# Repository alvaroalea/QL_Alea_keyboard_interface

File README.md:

# QL_Alea_keyboard_interface
A USB Keyboard Interface to install inside Sinclair QL Computer an replace the orignal Keyboard

## WARNING - THIS PROJECT IT'S INCOMPLETE
This is only some work in progress files.

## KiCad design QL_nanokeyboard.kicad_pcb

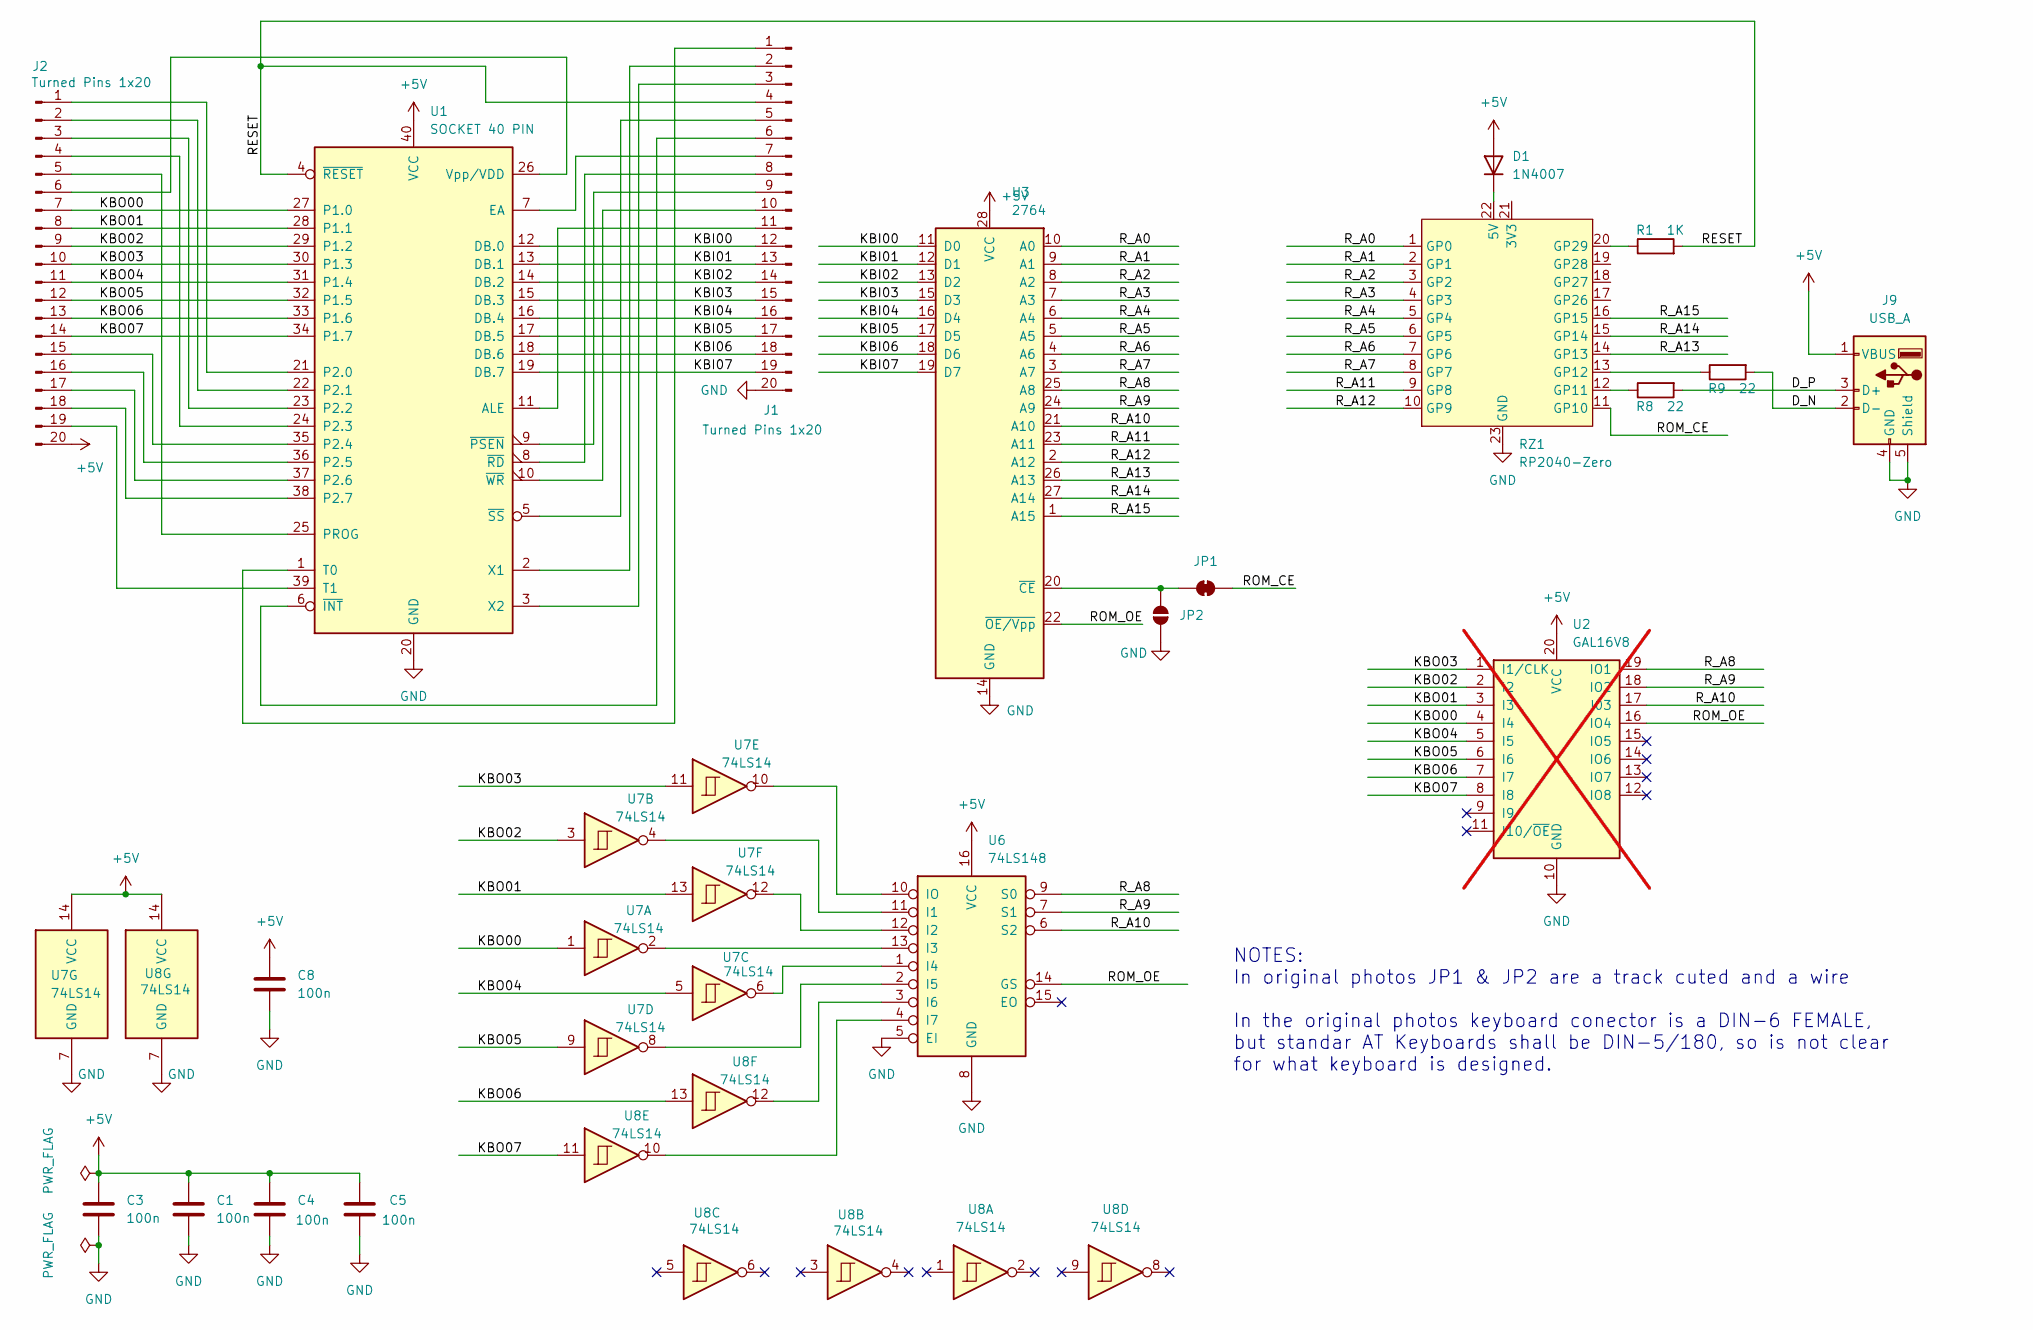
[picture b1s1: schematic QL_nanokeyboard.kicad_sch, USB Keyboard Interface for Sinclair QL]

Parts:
C1, C3, C4, C5: 100n; C_Disc_D4.3mm_W1.9mm_P5.00mm
C8: 100n; C_Disc_D5.0mm_W2.5mm_P5.00mm
D1: 1N4007; D_DO-35_SOD27_P7.62mm_Horizontal
J1, J2: Turned Pins 1x20; PinHeader_1x20_P2.54mm_Vertical
J9: USB_A; USB_A_Molex_67643_Horizontal
JP1: SolderJumper_2_Bridged; SolderJumper-2_P1.3mm_Bridged_Pad1.0x1.5mm
JP2: SolderJumper_2_Open; SolderJumper-2_P1.3mm_Open_Pad1.0x1.5mm
R1: 1K; R_Axial_DIN0207_L6.3mm_D2.5mm_P7.62mm_Horizontal
R8, R9: 22; R_Axial_DIN0207_L6.3mm_D2.5mm_P7.62mm_Horizontal
RZ1: RP2040-Zero
U1: SOCKET 40 PIN; DIP-40_W15.24mm_Socket
U2: GAL16V8; not fitted
U3: 2764; DIP-28_W15.24mm
U6: 74LS148; DIP-16_W7.62mm
U7, U8: 74LS14; DIP-14_W7.62mm

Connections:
+5V: C1.1, C3.1, C4.1, C5.2, C8.1, D1.2 (A), J2.20, J9.1 (VBUS), U1.40 (VCC), U2.20 (VCC), U3.28 (VCC), U6.16 (VCC), U7.14 (VCC), U8.14 (VCC)
/D_N: J9.2 (D-), R9.2
/D_P: J9.3 (D+), R8.2
/KBI00: J1.12, U1.12 (DB.0), U3.11 (D0)
/KBI01: J1.13, U1.13 (DB.1), U3.12 (D1)
/KBI02: J1.14, U1.14 (DB.2), U3.13 (D2)
/KBI03: J1.15, U1.15 (DB.3), U3.15 (D3)
/KBI04: J1.16, U1.16 (DB.4), U3.16 (D4)
/KBI05: J1.17, U1.17 (DB.5), U3.17 (D5)
/KBI06: J1.18, U1.18 (DB.6), U3.18 (D6)
/KBI07: J1.19, U1.19 (DB.7), U3.19 (D7)
/KBO00: J2.7, U1.27 (P1.0), U2.4 (I4), U7.1
/KBO01: J2.8, U1.28 (P1.1), U2.3 (I3), U7.13
/KBO02: J2.9, U1.29 (P1.2), U2.2 (I2), U7.3
/KBO03: J2.10, U1.30 (P1.3), U2.1 (I1/CLK), U7.11
/KBO04: J2.11, U1.31 (P1.4), U2.5 (I5), U7.5
/KBO05: J2.12, U1.32 (P1.5), U2.6 (I6), U7.9
/KBO06: J2.13, U1.33 (P1.6), U2.7 (I7), U8.13
/KBO07: J2.14, U1.34 (P1.7), U2.8 (I8), U8.11
/RESET: J1.4, R1.2, U1.4 (~RESET)
/ROM_CE: JP1.2 (B), RZ1.11 (GP10)
/ROM_OE: U2.16 (IO4), U3.22 (~OE/Vpp), U6.14 (GS)
/R_A0: RZ1.1 (GP0), U3.10 (A0)
/R_A1: RZ1.2 (GP1), U3.9 (A1)
/R_A2: RZ1.3 (GP2), U3.8 (A2)
/R_A3: RZ1.4 (GP3), U3.7 (A3)
/R_A4: RZ1.5 (GP4), U3.6 (A4)
/R_A5: RZ1.6 (GP5), U3.5 (A5)
/R_A6: RZ1.7 (GP6), U3.4 (A6)
/R_A7: RZ1.8 (GP7), U3.3 (A7)
/R_A8: U2.19 (IO1), U3.25 (A8), U6.9 (S0)
/R_A9: U2.18 (IO2), U3.24 (A9), U6.7 (S1)
/R_A10: U2.17 (I03), U3.21 (A10), U6.6 (S2)
/R_A11: RZ1.9 (GP8), U3.23 (A11)
/R_A12: RZ1.10 (GP9), U3.2 (A12)
/R_A13: RZ1.14 (GP13), U3.26 (A13)
/R_A14: RZ1.15 (GP14), U3.27 (A14)
/R_A15: RZ1.16 (GP15), U3.1 (A15)
GND: C1.2, C3.2, C4.2, C5.1, C8.2, J1.20, J9.4 (GND), J9.5 (Shield), JP2.1 (A), RZ1.23 (GND), U1.20 (GND), U2.10 (GND), U3.14 (GND), U6.5 (EI), U6.8 (GND), U7.7 (GND), U8.7 (GND)
unnamed: D1.1 (K), RZ1.22 (5V)
unnamed: J1.1, U1.1 (T0)
unnamed: J1.2, U1.2 (X1)
unnamed: J1.3, U1.3 (X2)
unnamed: J1.5, U1.5 (~SS)
unnamed: J1.6, U1.6 (~INT)
unnamed: J1.7, U1.7 (EA)
unnamed: J1.8, U1.8 (~RD)
unnamed: J1.9, U1.9 (~PSEN)
unnamed: J1.10, U1.10 (~WR)
unnamed: J1.11, U1.11 (ALE)
unnamed: J2.1, U1.21 (P2.0)
unnamed: J2.2, U1.22 (P2.1)
unnamed: J2.3, U1.23 (P2.2)
unnamed: J2.4, U1.24 (P2.3)
unnamed: J2.5, U1.25 (PROG)
unnamed: J2.6, U1.26 (Vpp/VDD)
unnamed: J2.15, U1.35 (P2.4)
unnamed: J2.16, U1.36 (P2.5)
unnamed: J2.17, U1.37 (P2.6)
unnamed: J2.18, U1.38 (P2.7)
unnamed: J2.19, U1.39 (T1)
unnamed: JP1.1 (A), JP2.2 (B), U3.20 (~CE)
unnamed: R8.1, RZ1.12 (GP11)
unnamed: R9.1, RZ1.13 (GP12)
unnamed: R1.1, RZ1.20 (GP29)
unnamed: U6.11 (I1), U7.4
unnamed: U6.12 (I2), U7.12
unnamed: U6.13 (I3), U7.2
unnamed: U6.1 (I4), U7.6
unnamed: U6.2 (I5), U7.8
unnamed: U6.3 (I6), U8.12
unnamed: U6.4 (I7), U8.10
unnamed: U6.10 (IO), U7.10

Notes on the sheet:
NOTES: In original photos JP1 & JP2 are a track cuted and a wire In the original photos keyboard conector is a DIN-6 FEMALE, but standar AT Keyboards shall be DIN-5/180, so is not clear for what keyboard is designed.

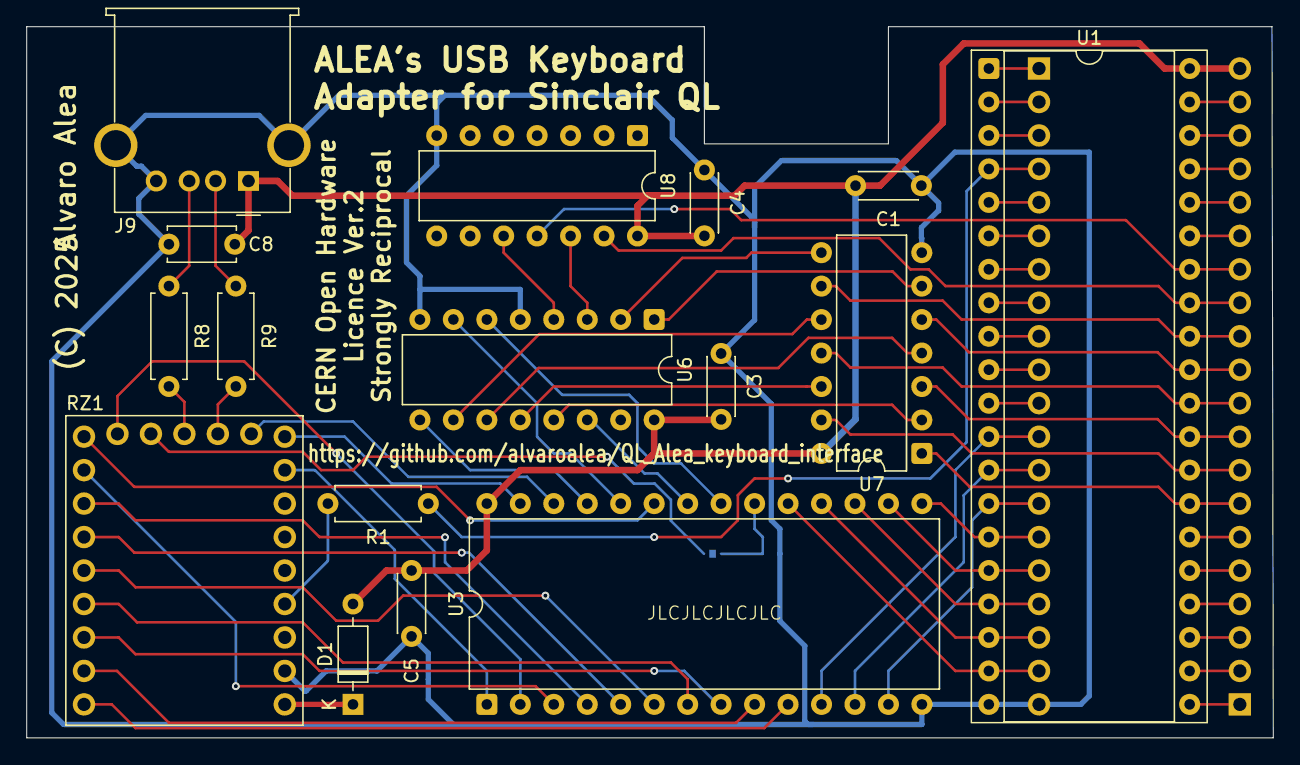
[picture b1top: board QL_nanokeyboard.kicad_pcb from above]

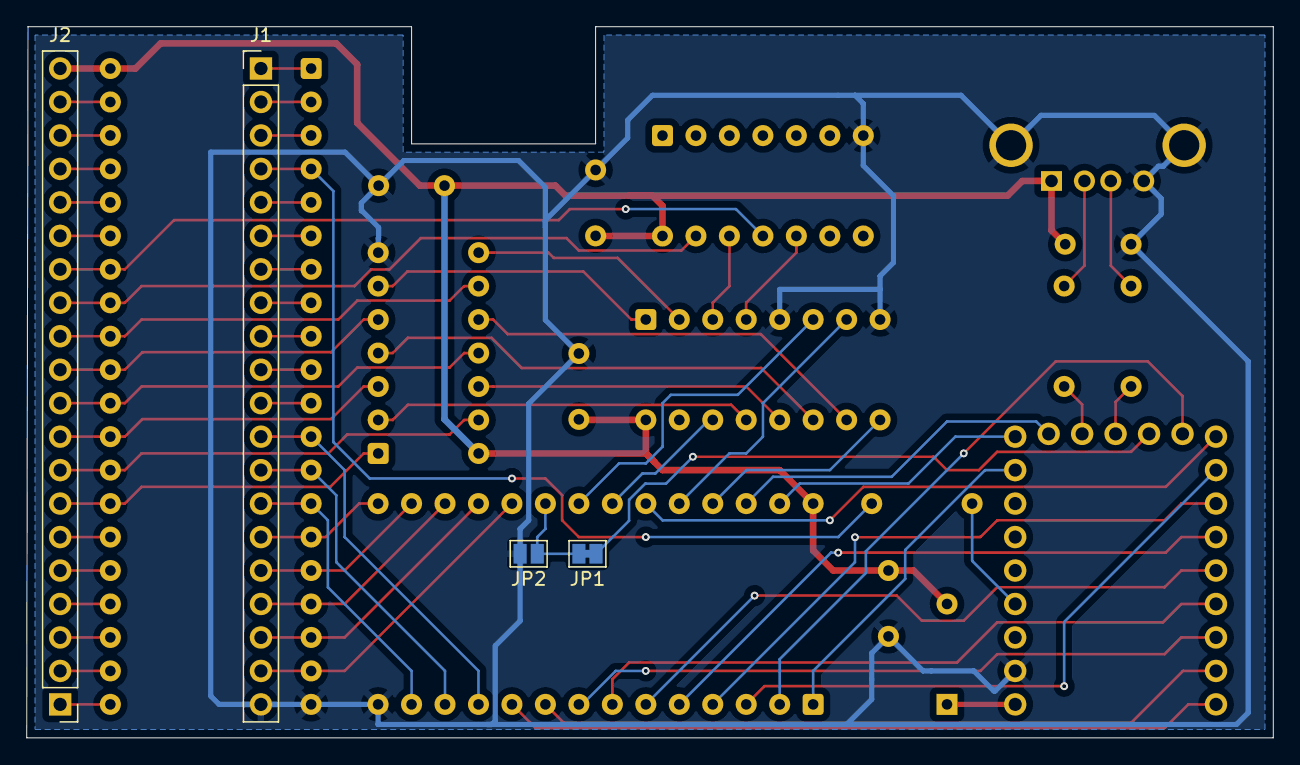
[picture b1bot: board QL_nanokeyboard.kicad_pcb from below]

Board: 2 copper layers, 94.6 x 54.0 mm, 20 parts (4 on the bottom side), 73 nets.

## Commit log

2025-05-20 initial
2025-07-18 add firmware source code
2025-07-30 release the key

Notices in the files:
QL_nanokeyboard.kicad_pcb:
(C) 2025
